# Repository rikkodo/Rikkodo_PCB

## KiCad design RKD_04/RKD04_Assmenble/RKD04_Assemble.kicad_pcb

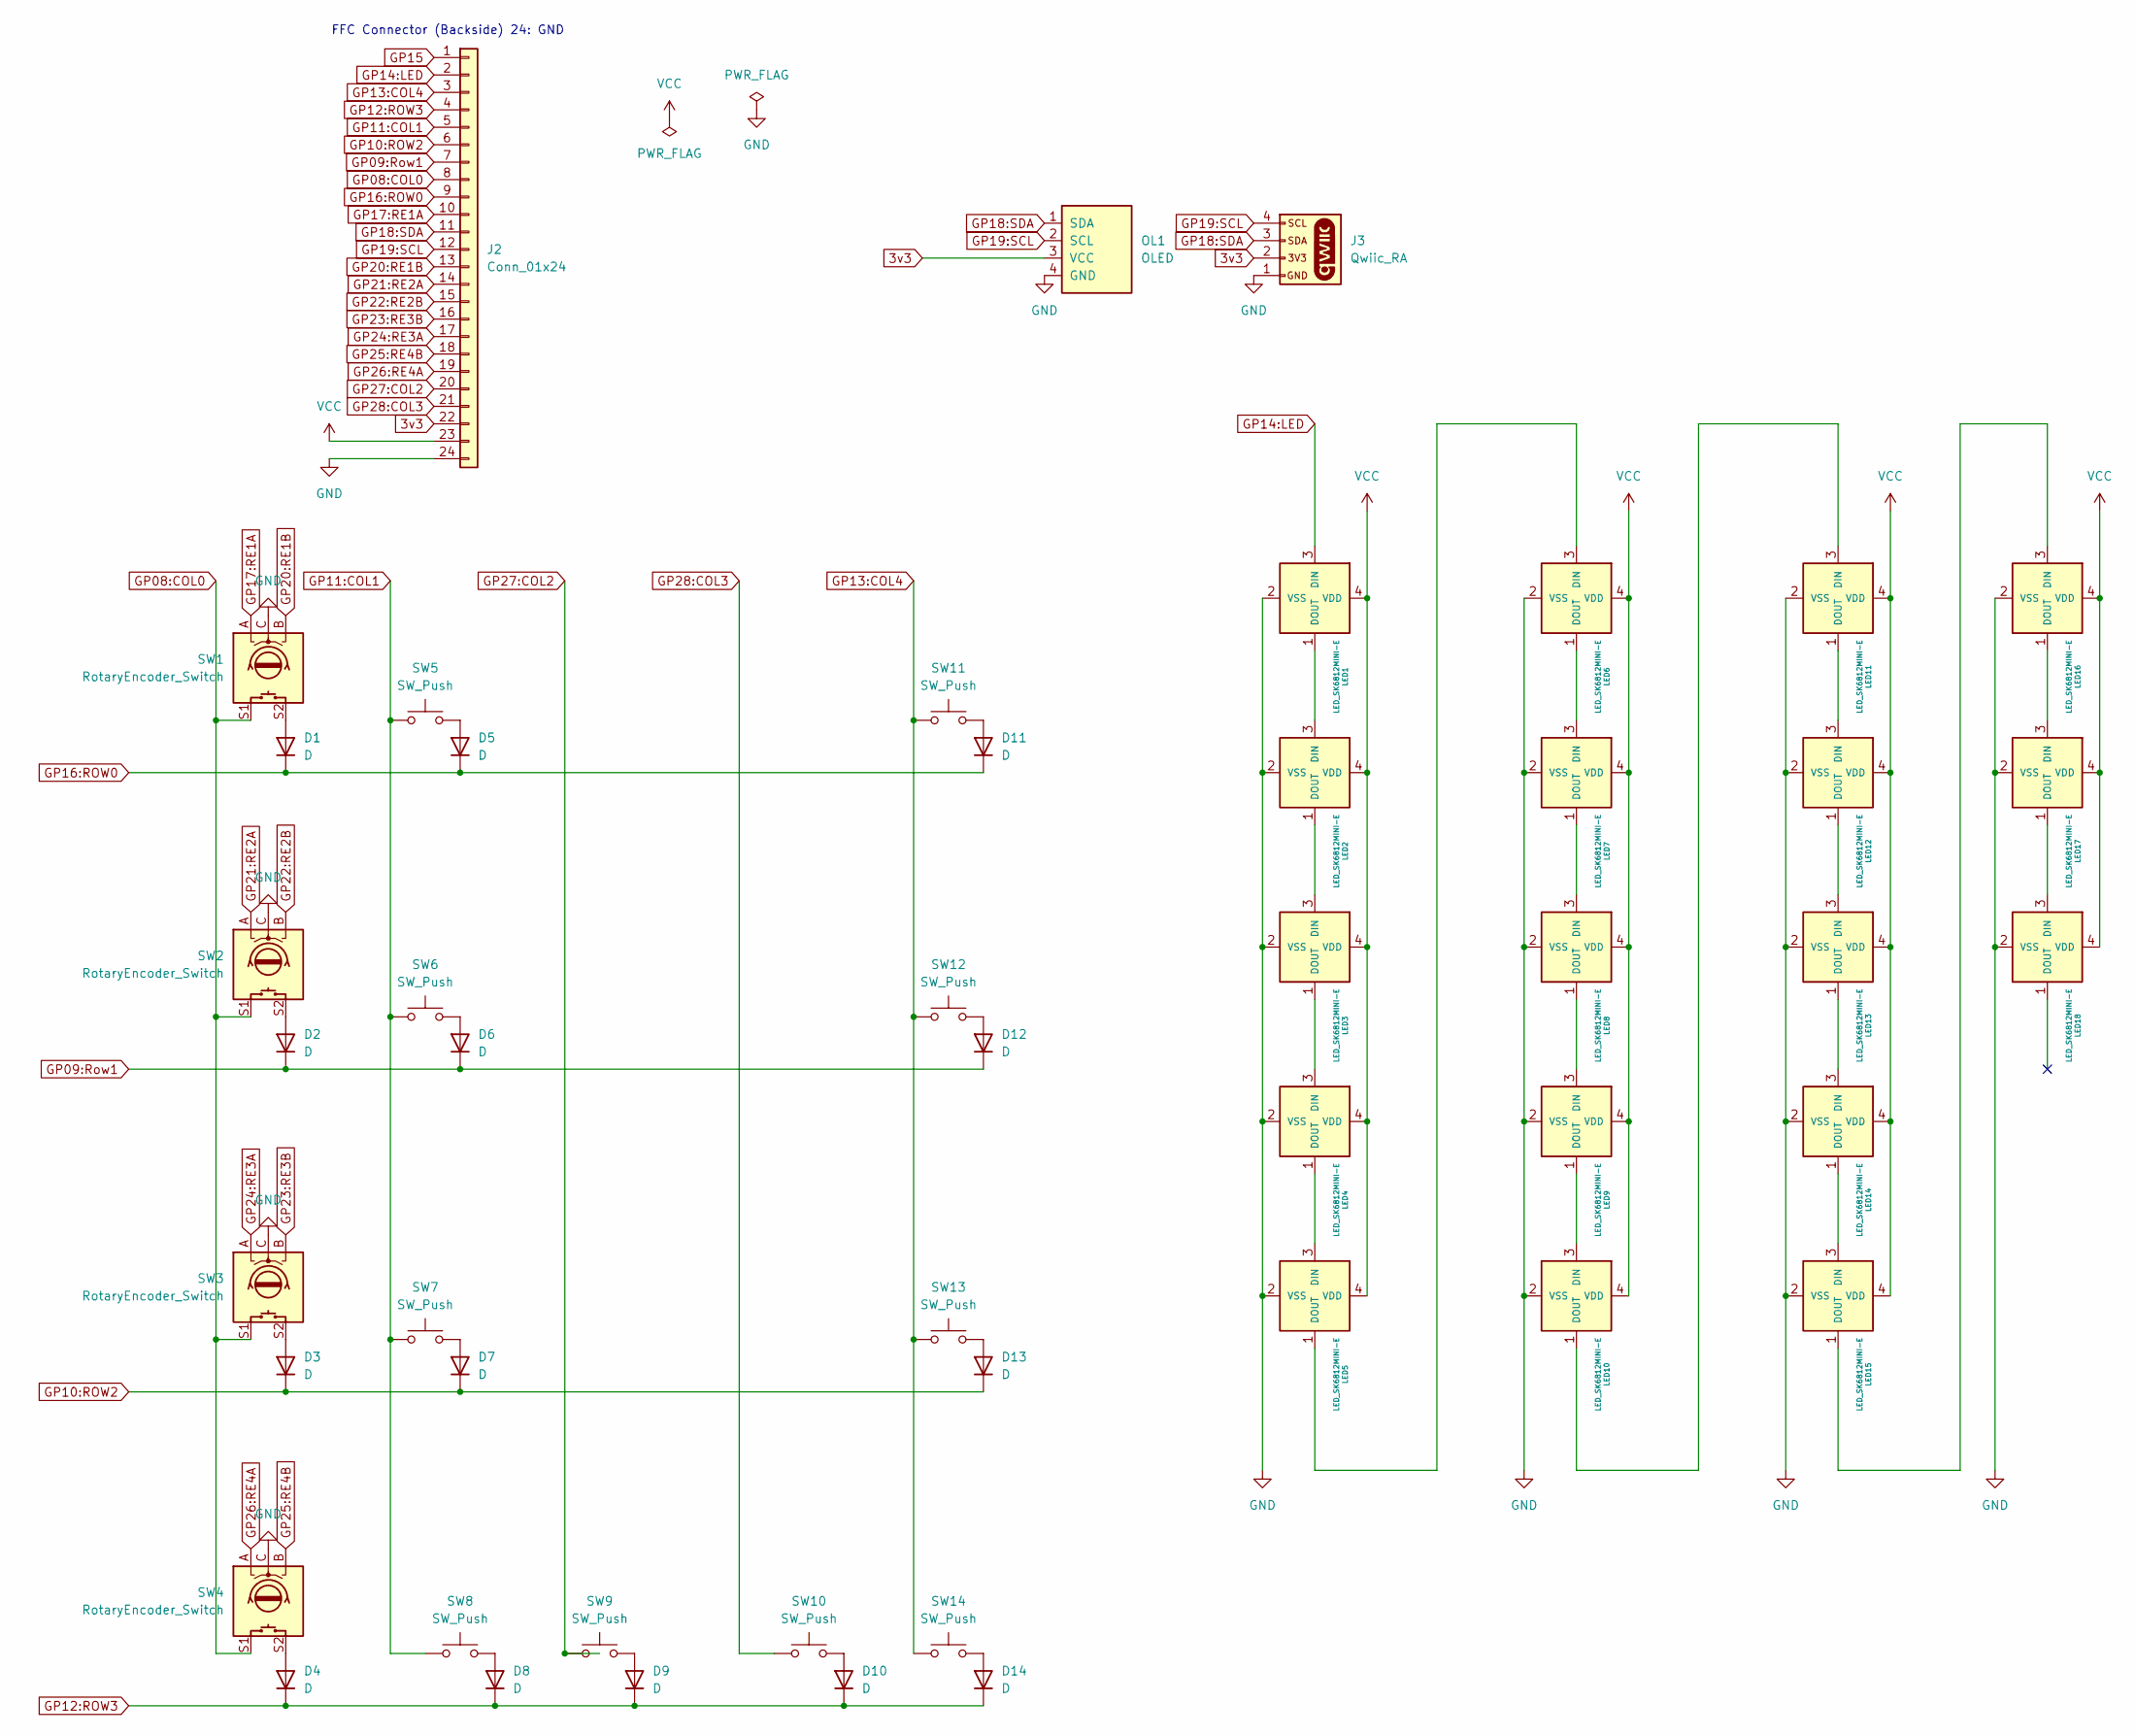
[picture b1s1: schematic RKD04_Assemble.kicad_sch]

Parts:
D1, D2, D3, D4, D5, D6, D7, D8, D9, D10, D11, D12, D13, D14: D; Diode_SMD
J2: Conn_01x24; Hirose_FH12-24S-0.5SH_1x24-1MP_P0.50mm_Horizontal
J3: Qwiic_RA; JST_SMD_1.0mm-4_Black
LED1, LED2, LED3, LED4, LED5, LED6, LED7, LED8, LED9, LED10, LED11, LED12, LED13, LED14, LED15, LED16, LED17, LED18: LED_SK6812MINI-E; LED_SK6812MINI-E_BL
OL1: OLED; OLED_center_display
SW1, SW2, SW3, SW4: RotaryEncoder_Switch; RotaryEncoder_EC11-Switch
SW5, SW6, SW7, SW8, SW9, SW10, SW11, SW12, SW13, SW14: SW_Push; rkd_Asm_ChocV1V2_Hotswap_1u

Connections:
3v3: J2.22, J3.2, OL1.3 (VCC)
GND: J2.24, J3.1, LED1.2 (VSS), LED2.2 (VSS), LED3.2 (VSS), LED4.2 (VSS), LED5.2 (VSS), LED6.2 (VSS), LED7.2 (VSS), LED8.2 (VSS), LED9.2 (VSS), LED10.2 (VSS), LED11.2 (VSS), LED12.2 (VSS), LED13.2 (VSS), LED14.2 (VSS), LED15.2 (VSS), LED16.2 (VSS), LED17.2 (VSS), LED18.2 (VSS), OL1.4 (GND), SW1.C, SW2.C, SW3.C, SW4.C
GP08:COL0: J2.8, SW1.S1, SW2.S1, SW3.S1, SW4.S1
GP09:Row1: D2.1 (K), D6.1 (K), D12.1 (K), J2.7
GP10:ROW2: D3.1 (K), D7.1 (K), D13.1 (K), J2.6
GP11:COL1: J2.5, SW5.2, SW6.2, SW7.2, SW8.2
GP12:ROW3: D4.1 (K), D8.1 (K), D9.1 (K), D10.1 (K), D14.1 (K), J2.4
GP13:COL4: J2.3, SW11.2, SW12.2, SW13.2, SW14.2
GP14:LED: J2.2, LED1.3 (DIN)
GP16:ROW0: D1.1 (K), D5.1 (K), D11.1 (K), J2.9
GP17:RE1A: J2.10, SW1.A
GP18:SDA: J2.11, J3.3, OL1.1 (SDA)
GP19:SCL: J2.12, J3.4, OL1.2 (SCL)
GP20:RE1B: J2.13, SW1.B
GP21:RE2A: J2.14, SW2.A
GP22:RE2B: J2.15, SW2.B
GP23:RE3B: J2.16, SW3.B
GP24:RE3A: J2.17, SW3.A
GP25:RE4B: J2.18, SW4.B
GP26:RE4A: J2.19, SW4.A
GP27:COL2: J2.20, SW9.2
GP28:COL3: J2.21, SW10.2
unnamed: D1.2 (A), SW1.S2
unnamed: D2.2 (A), SW2.S2
unnamed: D3.2 (A), SW3.S2
unnamed: D4.2 (A), SW4.S2
unnamed: D5.2 (A), SW5.1
unnamed: D6.2 (A), SW6.1
unnamed: D7.2 (A), SW7.1
unnamed: D8.2 (A), SW8.1
unnamed: D9.2 (A), SW9.1
unnamed: D10.2 (A), SW10.1
unnamed: D11.2 (A), SW11.1
unnamed: D12.2 (A), SW12.1
unnamed: D13.2 (A), SW13.1
unnamed: D14.2 (A), SW14.1
unnamed: LED1.1 (DOUT), LED2.3 (DIN)
unnamed: LED2.1 (DOUT), LED3.3 (DIN)
unnamed: LED3.1 (DOUT), LED4.3 (DIN)
unnamed: LED4.1 (DOUT), LED5.3 (DIN)
unnamed: LED5.1 (DOUT), LED6.3 (DIN)
unnamed: LED6.1 (DOUT), LED7.3 (DIN)
unnamed: LED7.1 (DOUT), LED8.3 (DIN)
unnamed: LED8.1 (DOUT), LED9.3 (DIN)
unnamed: LED9.1 (DOUT), LED10.3 (DIN)
unnamed: LED10.1 (DOUT), LED11.3 (DIN)
unnamed: LED11.1 (DOUT), LED12.3 (DIN)
unnamed: LED12.1 (DOUT), LED13.3 (DIN)
unnamed: LED13.1 (DOUT), LED14.3 (DIN)
unnamed: LED14.1 (DOUT), LED15.3 (DIN)
unnamed: LED15.1 (DOUT), LED16.3 (DIN)
unnamed: LED16.1 (DOUT), LED17.3 (DIN)
unnamed: LED17.1 (DOUT), LED18.3 (DIN)
VCC: J2.23, LED1.4 (VDD), LED2.4 (VDD), LED3.4 (VDD), LED4.4 (VDD), LED5.4 (VDD), LED6.4 (VDD), LED7.4 (VDD), LED8.4 (VDD), LED9.4 (VDD), LED10.4 (VDD), LED11.4 (VDD), LED12.4 (VDD), LED13.4 (VDD), LED14.4 (VDD), LED15.4 (VDD), LED16.4 (VDD), LED17.4 (VDD), LED18.4 (VDD)

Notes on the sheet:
FFC Connector (Backside) 24: GND

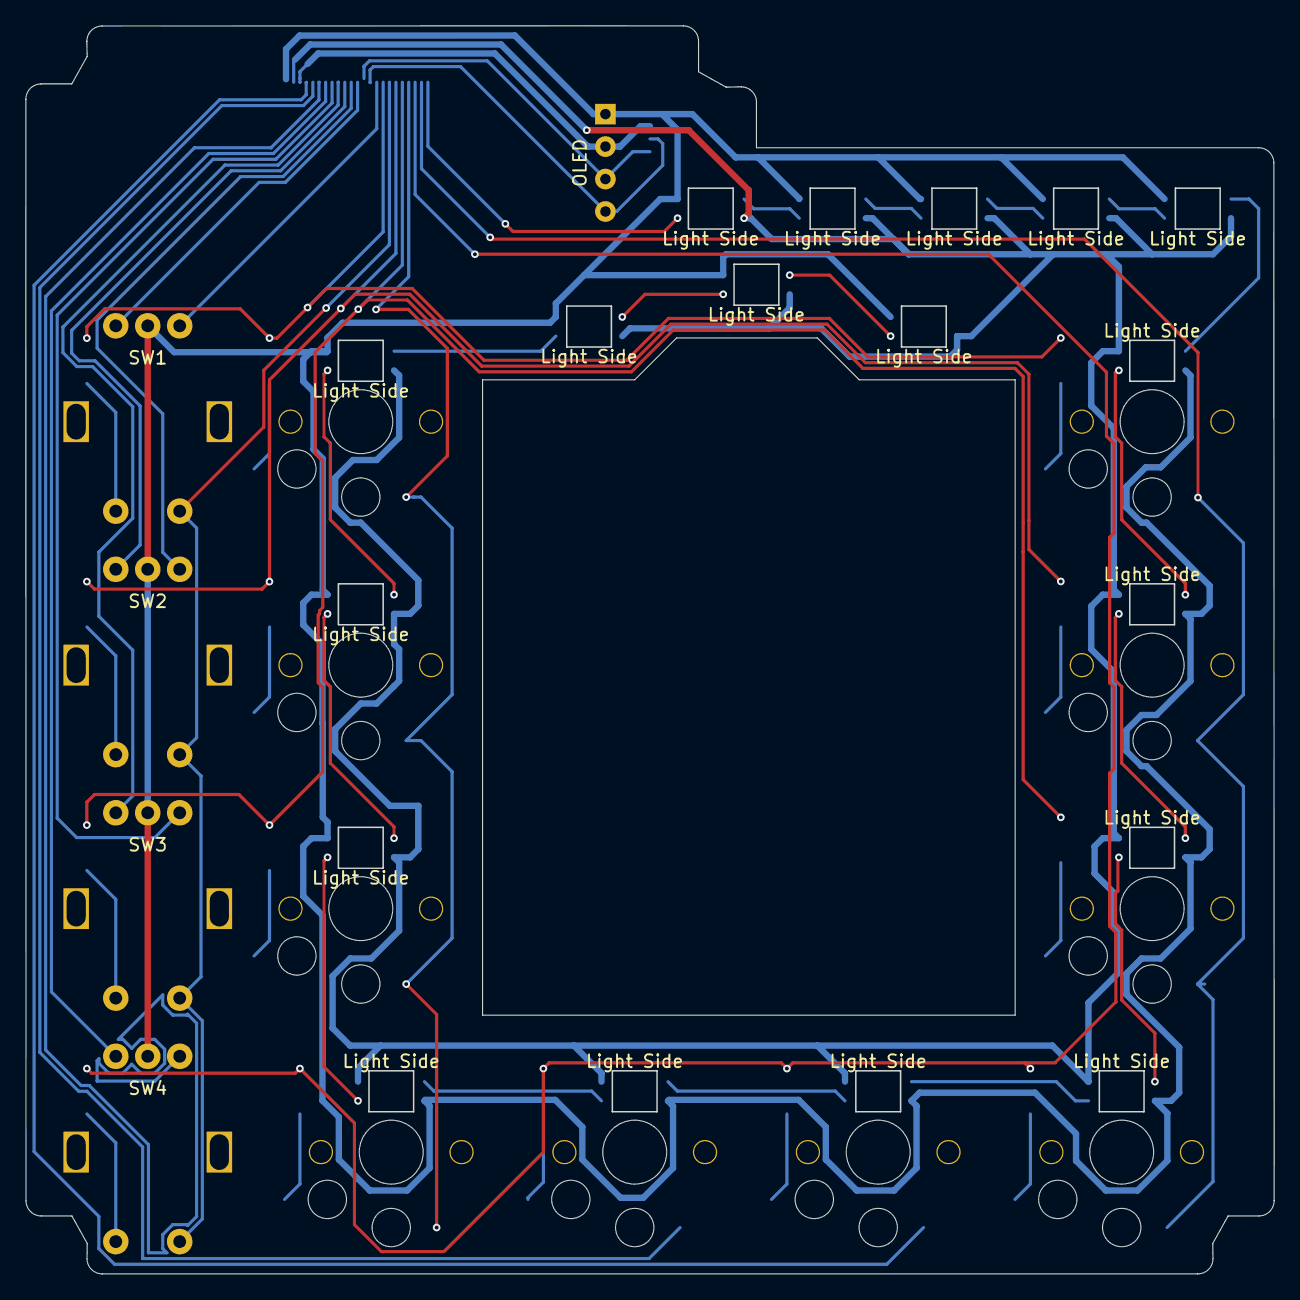
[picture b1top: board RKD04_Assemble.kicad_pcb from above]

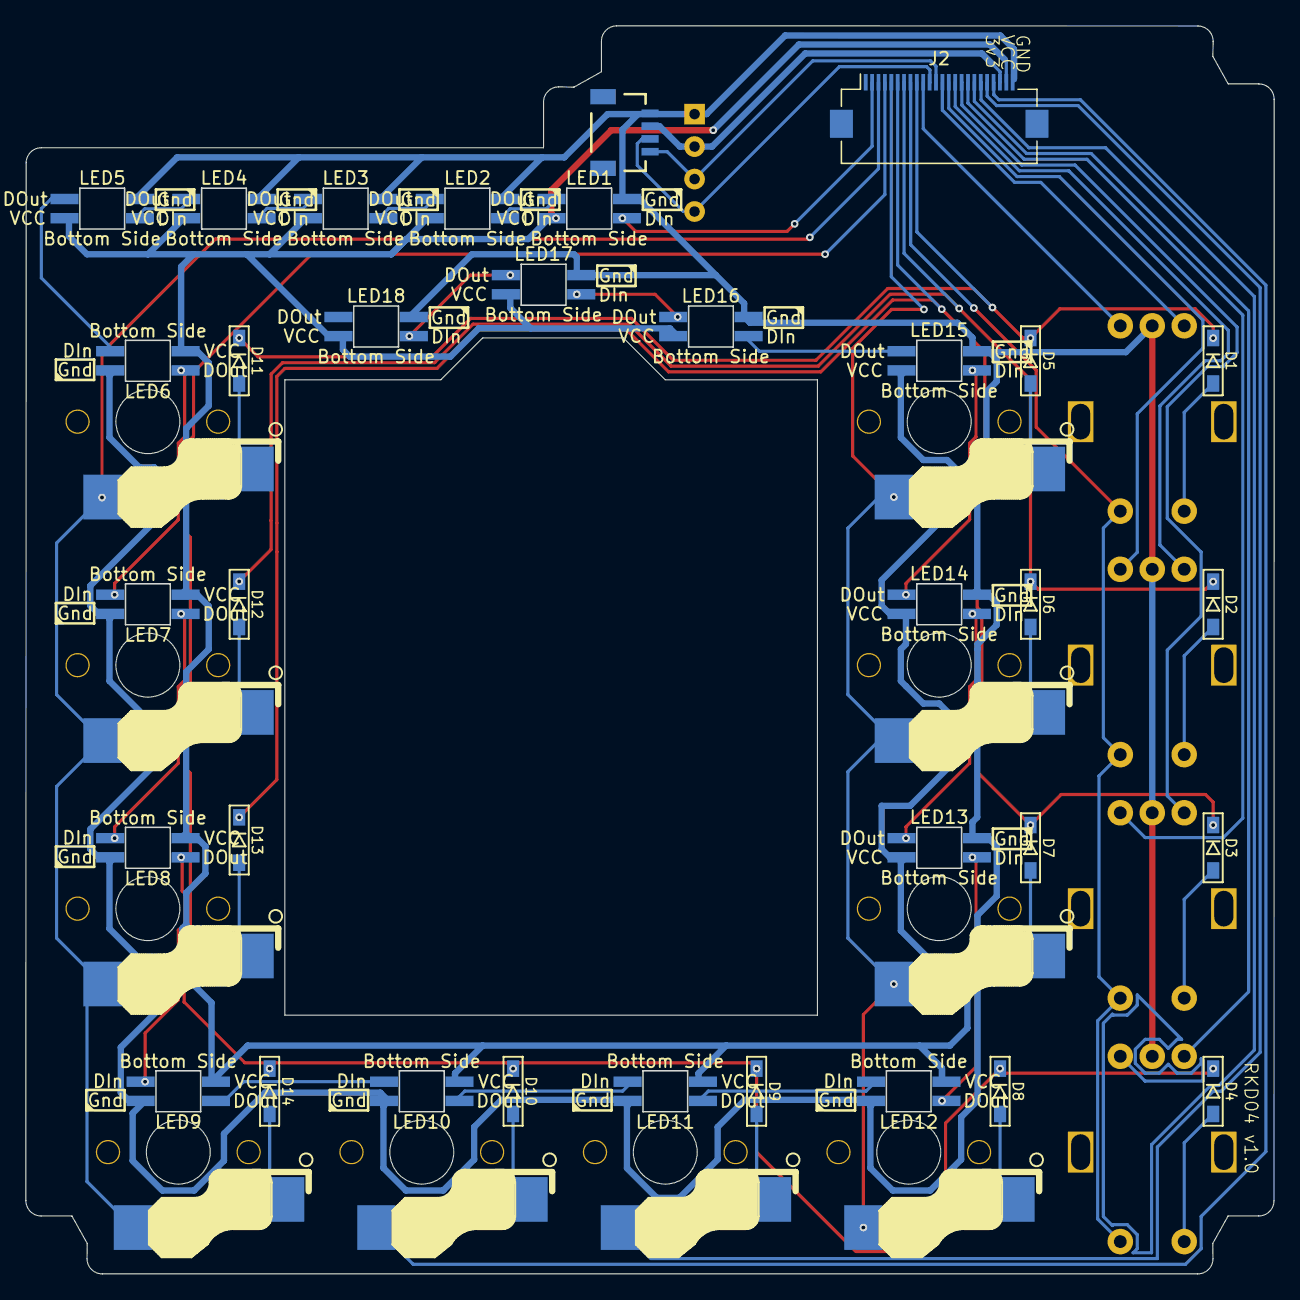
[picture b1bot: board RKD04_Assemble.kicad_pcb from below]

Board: 2 copper layers, 97.7 x 97.6 mm, 49 parts (2 on the bottom side), 54 nets.

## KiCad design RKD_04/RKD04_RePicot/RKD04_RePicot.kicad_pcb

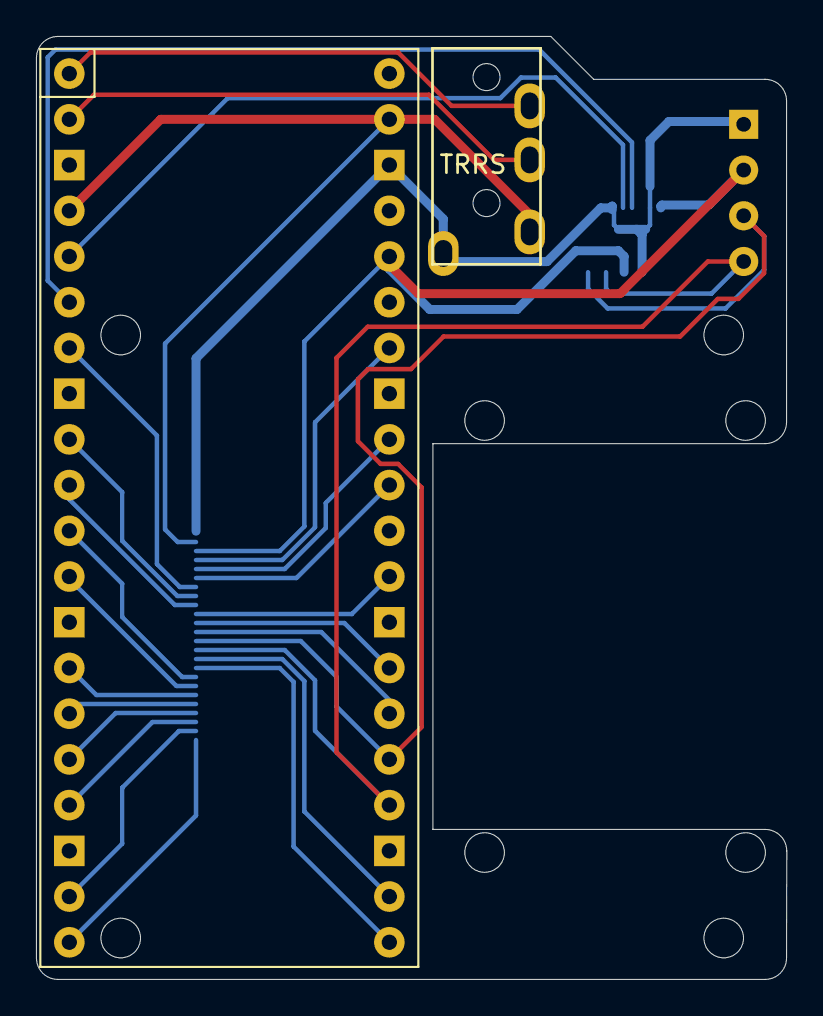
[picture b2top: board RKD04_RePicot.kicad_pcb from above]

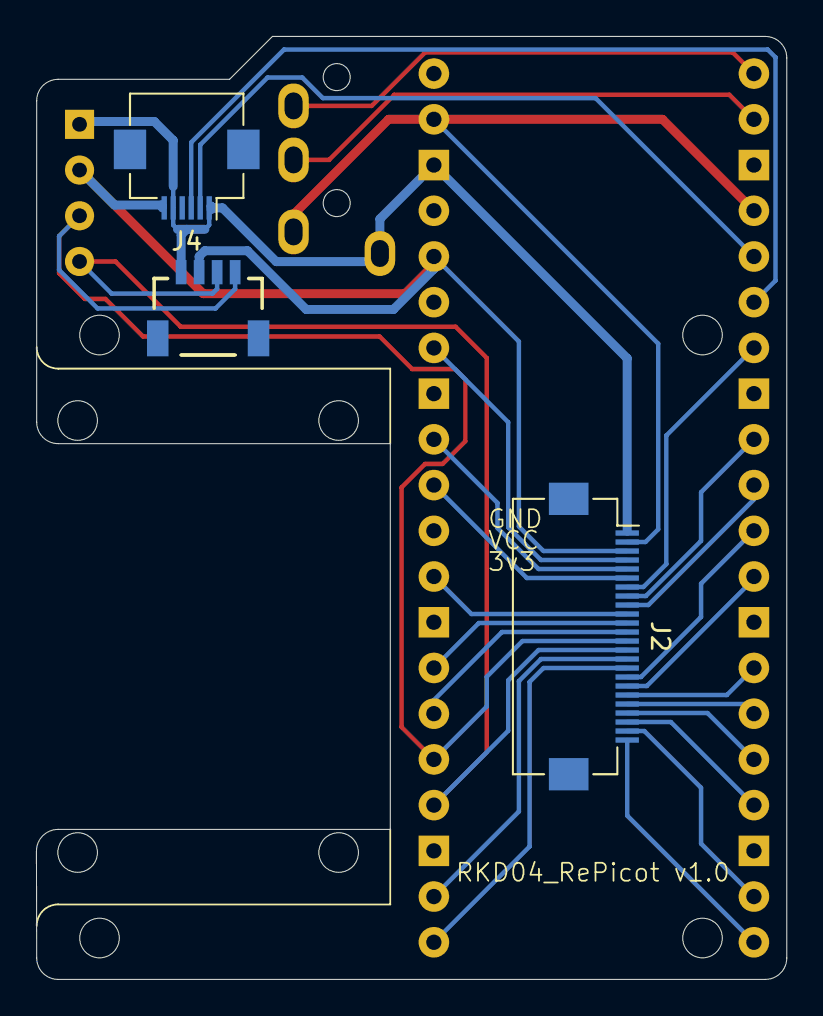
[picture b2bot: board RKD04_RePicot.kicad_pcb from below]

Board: 2 copper layers, 41.7 x 52.4 mm, 8 parts (3 on the bottom side), 28 nets.

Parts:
J1: TRRS; TRRS_PJ-320A
J2: Conn_01x24; Hirose_FH12-24S-0.5SH_1x24-1MP_P0.50mm_Horizontal
J3: Qwiic_RA; JST_SMD_1.0mm-4_Black
J4: Conn_01x06; Hirose_FH12-6S-0.5SH_1x06-1MP_P0.50mm_Horizontal
OL1: OLED; OLED_center_display
Picot**: rkd_picot5400_BTM
Point1: PointScrewHall; rkd_Point_Screw_Hall
U1: Pico; rkd_RPi_Pico_TH_NODBG

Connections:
3V3: J2.3, J3.2, J4.6, OL1.3 (VCC), U1.36 (3V3)
GND: J1.A, J2.1, J3.1, J4.1, J4.5, OL1.4 (GND), U1.38 (GND)
GP00:UART_TX: J1.B, U1.1 (GPIO0)
GP01:UART_RX: J1.C, U1.2 (GPIO1)
GP03:SCK: J4.2, U1.5 (GPIO3)
GP04:TX: J4.3, U1.6 (GPIO4)
GP08: J2.17, U1.11 (GPIO8)
GP09: J2.18, U1.12 (GPIO9)
GP10: J2.19, U1.14 (GPIO10)
GP11: J2.20, U1.15 (GPIO11)
GP12: J2.21, U1.16 (GPIO12)
GP13: J2.22, U1.17 (GPIO13)
GP14: J2.23, U1.19 (GPIO14)
GP15: J2.24, U1.20 (GPIO15)
GP16: J2.16, U1.21 (GPIO16)
GP17: J2.15, U1.22 (GPIO17)
GP18:SDA: J2.14, J3.3, OL1.1 (SDA), U1.24 (GPIO18)
GP19:SCL: J2.13, J3.4, OL1.2 (SCL), U1.25 (GPIO19)
GP20: J2.12, U1.26 (GPIO20)
GP21: J2.11, U1.27 (GPIO21)
GP22: J2.10, U1.29 (GPIO22)
GP23: J2.9, U1.10 (GPIO7)
GP24: J2.8, U1.9 (GPIO6)
GP25: J2.7, U1.7 (GPIO5)
GP26: J2.6, U1.31 (GPIO26_ADC0)
GP27: J2.5, U1.32 (GPIO27_ADC1)
GP28: J2.4, U1.34 (GPIO28_ADC2)
VCC: J1.D, J2.2, U1.4 (GPIO2), U1.39 (VSYS)
